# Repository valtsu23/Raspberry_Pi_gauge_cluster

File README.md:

# Raspberry_Pi_gauge_cluster
### Check out also new improved version: https://github.com/valtsu23/DIY-Emu-Black-Dash

Video: https://youtu.be/ISC5q4k9wDg

### Updates
30.8.2023 display_v2.py released (more info on the file)

### How it works
Adafruit Feather receives messages from Can Bus and picks rpm signal for shift light. Feather sends same can bus data bytes over Uart to Raspberry pi. 
Feather reads the amount of ambient light from photodiode and controls screeen brightness with pwm. 
Device needs switched 12V and continous 12v from battery to work correctly. Switched power wakes up the device and Raspberry pi starts booting. When Can Bus stream is lost Raspberry pi automatically starts shutdown process and sends message to Feather. After specified time the Feather turns off the relay connected to continous 12v and cuts power from the device. The device doesn't consume any power after shutdown. 

### Something to improve
- More testing needed
- Adding Raspberry pi setup guide
- Shortening the start up time (about 25 seconds now)

### Technical specs:
- Raspberry Pi 4 Model B 4GB
- SanDisk Extreme Pro UHS-I U3 64GB microSD
- 5" sunlight readable display with touchscreen from Makerplane:
  - https://store.makerplane.org/5-sunlight-readable-touchscreen-hdmi-display-for-raspberry-pi/
- DIY PCB inside the enclosure controls power for all devices and receives Can Bus messages and sends them over UART to Raspberry pi
  - DC-DC converter
  - Adafruit Feather M4 CAN Express with ATSAME51
  - Adafruit DS3231 Precision RTC - STEMMA QT
  - Screen brightness control
  - Adafruit Neopixel shiftlight control
  - Small relay for power

### Software specs
- Raspberry Pi OS Lite 64bit (bullseye)
  - X server: X.Org
  - Window manager: Openbox
  - Gauge cluster software is based on Pygame graphics library
### Graphic software functions
- There is 6 sensors data (3 left and 3 right) that you can choose to display with touscreen
- bar on the bottom of the screen in normal situation is blue and shows Raspberry pi CPU temperature
- If there is some error detected by ECU or battery voltage is low. Error flags are shown on the bottom of the screen and the bar is red
  
### Can bus data
- Most of the data needed is read from Ecumaster Emu Black can stream
- There is also DIY can bus device sending message id 0x400, which contains
  - Turn signals
  - High beam on
  - Fuel level
  - Ambient temperature

### Case
- Designed with FreeCAD
- Filament is PETG
- M3x6 machine screws 2 pcs
- M4 thread insert 1 pcs
- M4x8 machine screw 1pcs
- M4x20 machine screw 2pcs
- M4 nut 2pcs

### Part list for PCB:
#### From www.partco.fi
  - PCH2596S DC-DC converter (LM2596S)
  - 3A diode 
  - 1A diode 2pcs
  - FTR-F3AA005V (small 5V relay)
  - BPW42 3mm phototransistor or similar
  - 2N3904 NPN transistor or similar
  - B3F-31XX Omron switch or SKH KKK 2 from partco.fi
  - 2k2 0,6w resistor
  - 1M 0,6w resistor 
  - 2x13 male pin header with long pins (20mm total length)
  - 2x13 female smd pin header (soldered to display pcb)
  - 1x40 female pin header
  - 1x40 male pin header
  - 0,22mm2 - 0,5mm2 wires (0,5mm2 recommended for power and ground)
#### From Berrybase.de
  - NeoPixel Stick mit 8 WS2812 5050 RGB LEDs (Copy of Adafruit's product. Dimensions won't match)
#### From www.adafruit.com
  - Adafruit DS3231 Precision RTC - STEMMA QT
  - Adafruit Feather M4 CAN Express with ATSAME51
#### From www.ebay.com
  - 5pin JST-SM connector pair

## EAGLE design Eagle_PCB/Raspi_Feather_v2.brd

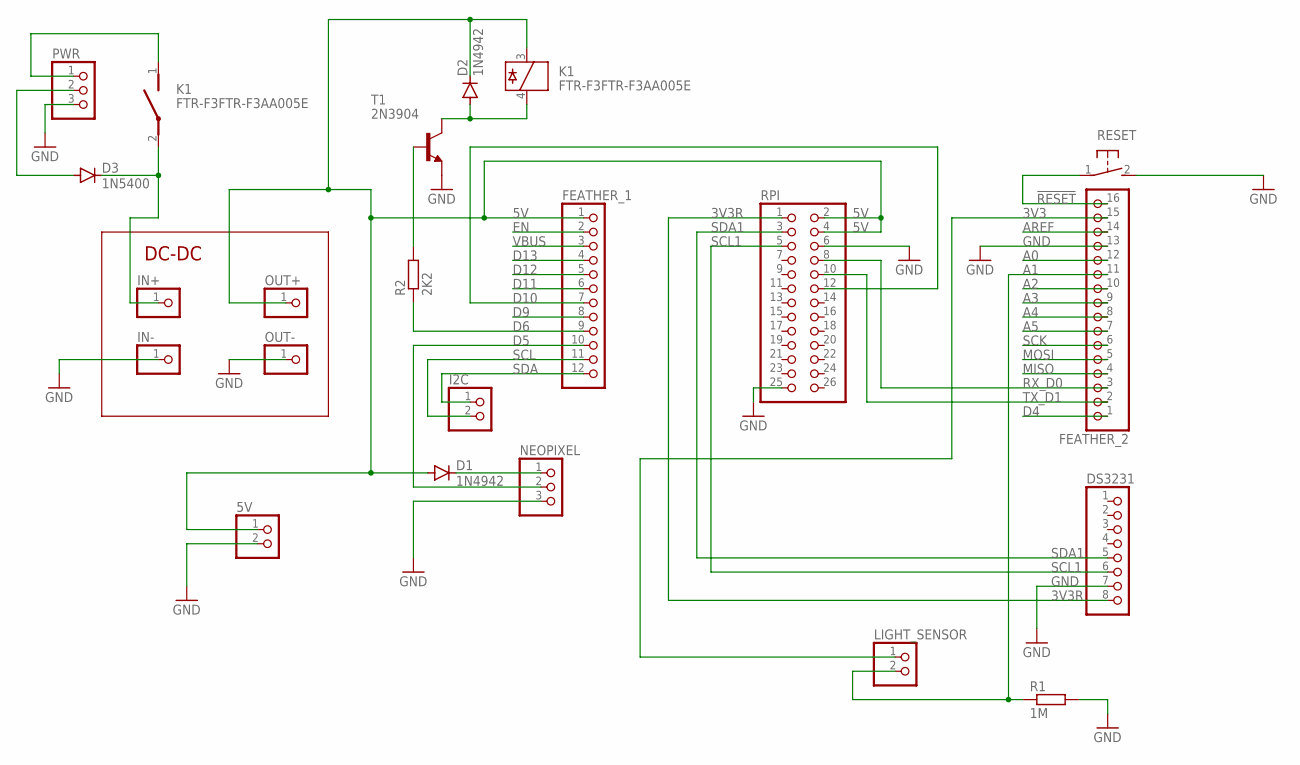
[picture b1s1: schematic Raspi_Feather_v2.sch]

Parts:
5V: PINHD-1X2; 1X02
D1, D2: 1N4942; DO41-10
D3: 1N5400; DO201-15
DS3231: PINHD-1X8; 1X08
FEATHER_1: HEADER-1X12; 1X12_ROUND
FEATHER_2: HEADER-1X16ROUND; 1X16_ROUND
I2C: PINHD-1X2; 1X02
IN+: PINHD-1X1; 1X01
IN-: PINHD-1X1; 1X01
K1: FTR-F3FTR-F3AA005E; REED
LIGHT_SENSOR: PINHD-1X2; 1X02
NEOPIXEL: PINHD-1X3; 1X03
OUT+: PINHD-1X1; 1X01
OUT-: PINHD-1X1; 1X01
PWR: PINHD-1X3; 1X03
R1: 1M; 0207/7
R2: 2K2; 0207/10
RESET: 31-XX; B3F-31XX
RPI: PINHD-2X13; 2X13
T1: 2N3904; TO92

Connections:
3V3: FEATHER_2.15, LIGHT_SENSOR.1
3V3R: DS3231.8, RPI.1
5V: 5V.1, D1.A, D2.C, FEATHER_1.1, K1.3, OUT+.1, RPI.2, RPI.4
!RESET: FEATHER_2.16, RESET.1
A0: FEATHER_2.12
A1: FEATHER_2.11, LIGHT_SENSOR.2, R1.1
A2: FEATHER_2.10
A3: FEATHER_2.9
A4: FEATHER_2.8
A5: FEATHER_2.7
AREF: FEATHER_2.14
D4: FEATHER_2.1
D5: FEATHER_1.10, NEOPIXEL.2
D6: FEATHER_1.9, R2.1
D9: FEATHER_1.8
D10: FEATHER_1.7, RPI.12
D11: FEATHER_1.6
D12: FEATHER_1.5
D13: FEATHER_1.4
EN: FEATHER_1.2
GND: 5V.2, DS3231.7, FEATHER_2.13, IN-.1, NEOPIXEL.3, OUT-.1, PWR.3, R1.2, RESET.2 (S), RPI.6, RPI.25, T1.3 (E)
IN+: D3.C, IN+.1, K1.2
IN_CO: K1.1, PWR.1
IN_SW: D3.A, PWR.2
MISO: FEATHER_2.4
MOSI: FEATHER_2.5
unnamed: D1.C, NEOPIXEL.1
unnamed: R2.2, T1.2 (B)
unnamed: D2.A, K1.4, T1.1 (C)
RX_D0: FEATHER_2.3, RPI.8
SCK: FEATHER_2.6
SCL: FEATHER_1.11, I2C.2
SCL1: DS3231.6, RPI.5
SDA: FEATHER_1.12, I2C.1
SDA1: DS3231.5, RPI.3
TX_D1: FEATHER_2.2, RPI.10
VBUS: FEATHER_1.3

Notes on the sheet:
DC-DC

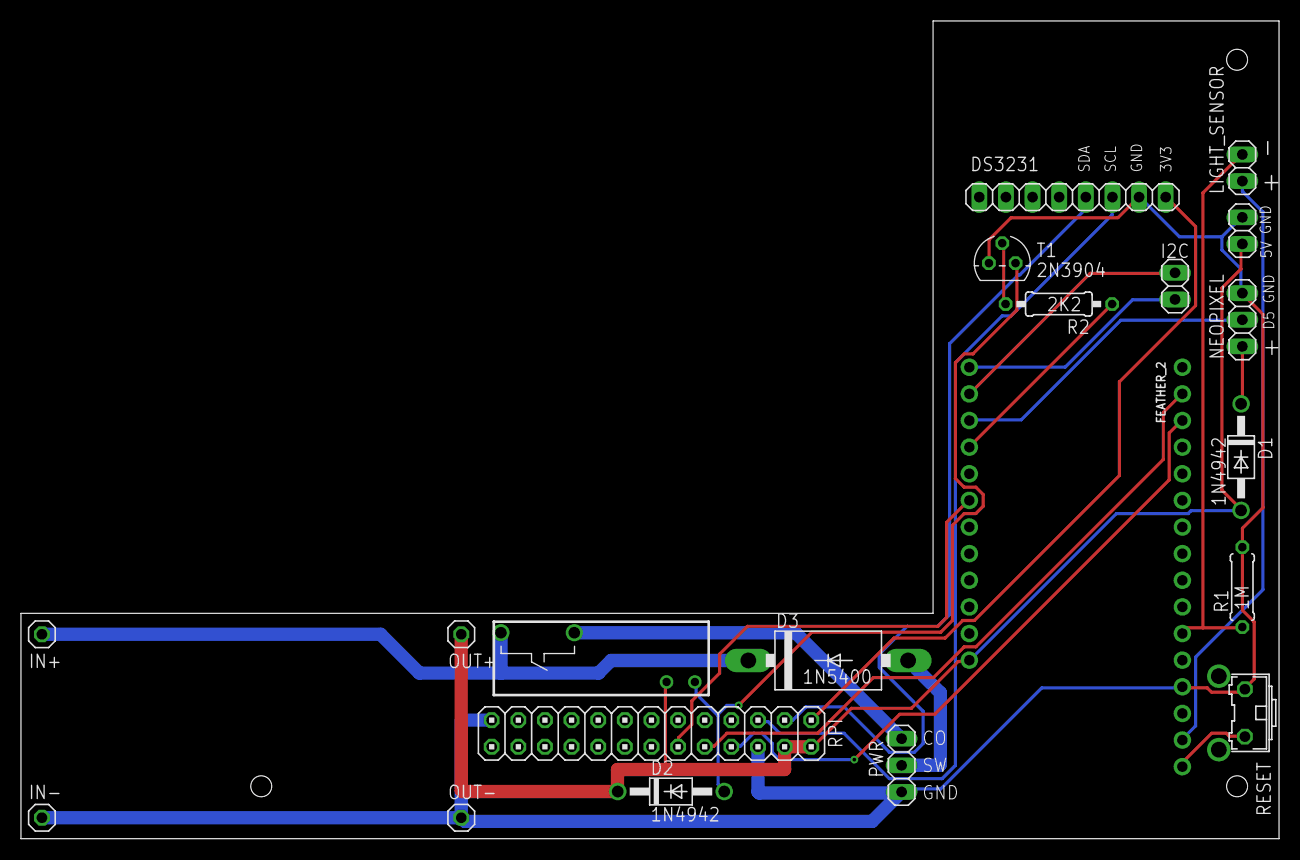
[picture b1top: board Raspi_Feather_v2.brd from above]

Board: 2 copper layers, 120.0 x 78.0 mm, 21 parts (0 on the bottom side), 21 nets.

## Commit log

2023-08-16 Update code.py
    fail_safe 30 -> 60
2023-08-18 Photodiode pull down resistor changed
    From 150k -> 1M, for better adc scale
2023-08-18 Update README.md
    Photodiode pull down resistor changed from 150k -> 1M, for better adc scale.
2023-08-18 Update code.py
    Photodiode pull down resistor has changed from 150k -> 1M, for better adc scale.

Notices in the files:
parts and their libraries:
microbuilder: This work is placed in the public domain, and may be freely used for commercial and non-commercial work with the following conditions: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
